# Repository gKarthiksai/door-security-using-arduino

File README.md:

# door-security-using-arduino
This includes the picture of the circuit, the schematic, the PCB schematic and the board file (the PCB layout/design is made only for Autocad Eagle users).

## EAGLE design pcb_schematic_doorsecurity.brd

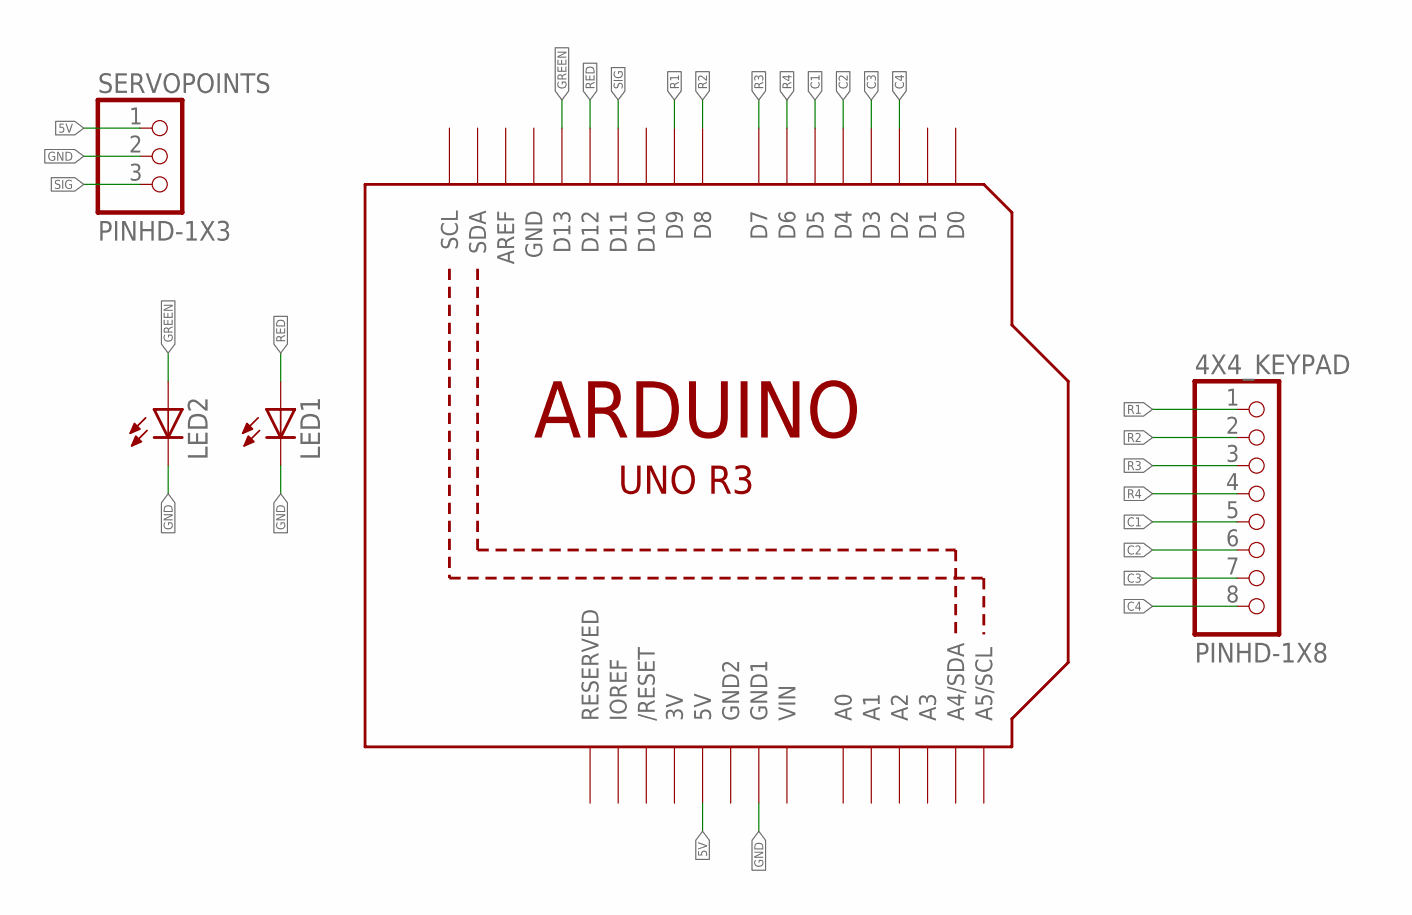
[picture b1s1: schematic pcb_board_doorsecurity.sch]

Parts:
4X4_KEYPAD: PINHD-1X8; 1X08
LED1, LED2: LED5MM
SERVOPOINTS: PINHD-1X3; 1X03
U1: ARDUINOR3-BPLACE

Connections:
3V: U1.3V
5V: SERVOPOINTS.1, U1.5V
C1: 4X4_KEYPAD.5, U1.D5
C2: 4X4_KEYPAD.6, U1.D4
C3: 4X4_KEYPAD.7, U1.D3
C4: 4X4_KEYPAD.8, U1.D2
GND: LED1.K (C), LED2.K (C), SERVOPOINTS.2, U1.GND, U1.GND1
GND2: U1.GND2
GREEN: LED2.A, U1.D13
R1: 4X4_KEYPAD.1, U1.D9
R2: 4X4_KEYPAD.2, U1.D8
R3: 4X4_KEYPAD.3, U1.D7
R4: 4X4_KEYPAD.4, U1.D6
RED: LED1.A, U1.D12
SIG: SERVOPOINTS.3, U1.D11
VIN: U1.VIN

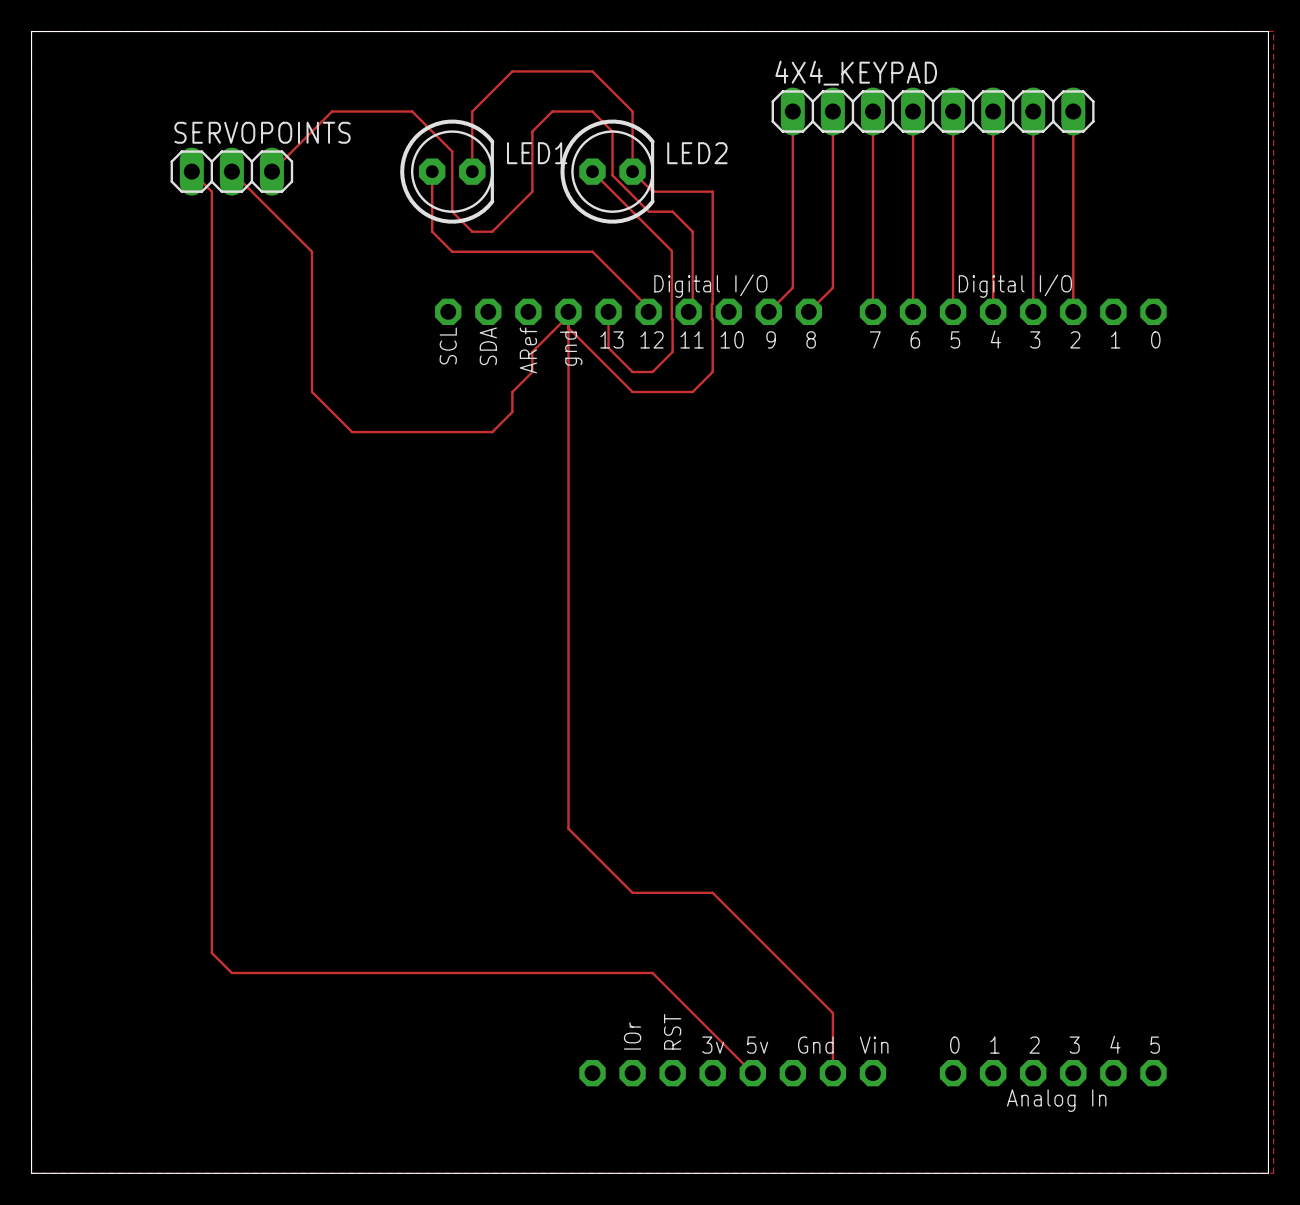
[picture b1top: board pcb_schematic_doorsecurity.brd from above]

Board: 2 copper layers, 78.4 x 72.4 mm, 5 parts (0 on the bottom side), 13 nets.

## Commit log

2022-10-05 Add files via upload
    Have a look through all of the files and make your very own "door security system".
    I have also included a demo video (demoVid) for more clarity on the working of the hardware.
